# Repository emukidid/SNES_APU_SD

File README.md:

# SNES_APU_SD
Drives a SNES APU from early Super Nintendo/Super Famicom consoles with an arduino to load tracks from SD Card

Based on code written by [CaitSith2]

### Current Features
- Loads a .spc file from SD card and plays it on the SNES APU
- Loads a .spc file through the PC interface.
- 16x2 LCD for track display and menu
- Menu with file selection
- SRAM to cache tracks (CaitSith2)
- Interface APU as direct memory (CaitSith2)

### Planned Features
- RTC for nice things

### Hardware required
- Early NTSC SNES or Super Famicom with modular APU
- Arduino Mega
- APU Arduino Shield (Work In Progress)
- Love for 16-bit SNES music

[caitsith2]:  <https://www.caitsith2.com/snes/apu.htm>

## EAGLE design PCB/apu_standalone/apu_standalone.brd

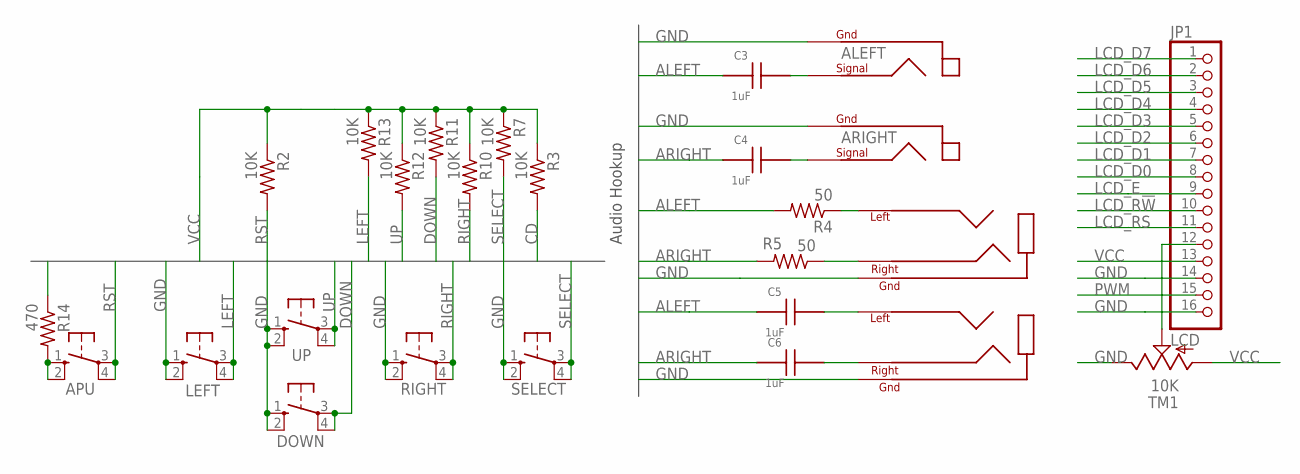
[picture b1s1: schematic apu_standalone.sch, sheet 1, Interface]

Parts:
APU: Reset; B3F-10XX
C3, C4, C5, C6: 1uF; C0805
DOWN: DOWN; B3F-10XX
JP1: LCD; 1X16
LEFT: LEFT; B3F-10XX
R2, R3, R7, R10, R11, R12, R13: 10K; R0805
R4, R5: 50; R0805
R14: 470; R0805
RIGHT: RIGHT; B3F-10XX
SELECT: SELECT; B3F-10XX
TM1: 10K; CA6H
U$2, U$3: HEADPHONE; SJ1-3533N
U$4, U$5: RCA; RCJ-01X
UP: UP; B3F-10XX

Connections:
ALEFT: C3.1, C5.1, R4.2; also elsewhere on the board
ARIGHT: C4.1, C6.1, R5.2; also elsewhere on the board
CD: R3.2; also elsewhere on the board
DOWN: DOWN.3, DOWN.4 (P1), R11.2; also elsewhere on the board
GND: DOWN.1 (S), DOWN.2 (S1), JP1.14, JP1.16, LEFT.1 (S), LEFT.2 (S1), R14.1, RIGHT.1 (S), RIGHT.2 (S1), SELECT.1 (S), SELECT.2 (S1), TM1.E, U$2.GND, U$3.GND, U$4.PGND1, U$4.PGND2, U$4.PGND3, U$5.PGND1, U$5.PGND2, U$5.PGND3, UP.1 (S), UP.2 (S1); also elsewhere on the board
LCD_D0: JP1.8; also elsewhere on the board
LCD_D1: JP1.7; also elsewhere on the board
LCD_D2: JP1.6; also elsewhere on the board
LCD_D3: JP1.5; also elsewhere on the board
LCD_D4: JP1.4; also elsewhere on the board
LCD_D5: JP1.3; also elsewhere on the board
LCD_D6: JP1.2; also elsewhere on the board
LCD_D7: JP1.1; also elsewhere on the board
LCD_E: JP1.9; also elsewhere on the board
LCD_R!W: JP1.10; also elsewhere on the board
LCD_RS: JP1.11; also elsewhere on the board
LEFT: LEFT.3, LEFT.4 (P1), R13.2; also elsewhere on the board
unnamed: C3.2, U$4.PSIG
unnamed: C4.2, U$5.PSIG
unnamed: C5.2, U$3.LEFT
unnamed: APU.1 (S), APU.2 (S1), R14.2
unnamed: C6.2, U$3.RIGHT
unnamed: R4.1, U$2.LEFT
unnamed: R5.1, U$2.RIGHT
unnamed: JP1.12, TM1.S
PWM: JP1.15; also elsewhere on the board
RIGHT: R10.2, RIGHT.3, RIGHT.4 (P1); also elsewhere on the board
RST: APU.3, APU.4 (P1), R2.2; also elsewhere on the board
SELECT: R7.2, SELECT.3, SELECT.4 (P1); also elsewhere on the board
UP: R12.2, UP.3, UP.4 (P1); also elsewhere on the board
VCC: JP1.13, R2.1, R3.1, R7.1, R10.1, R11.1, R12.1, R13.1, TM1.A; also elsewhere on the board

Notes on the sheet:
Audio Hookup

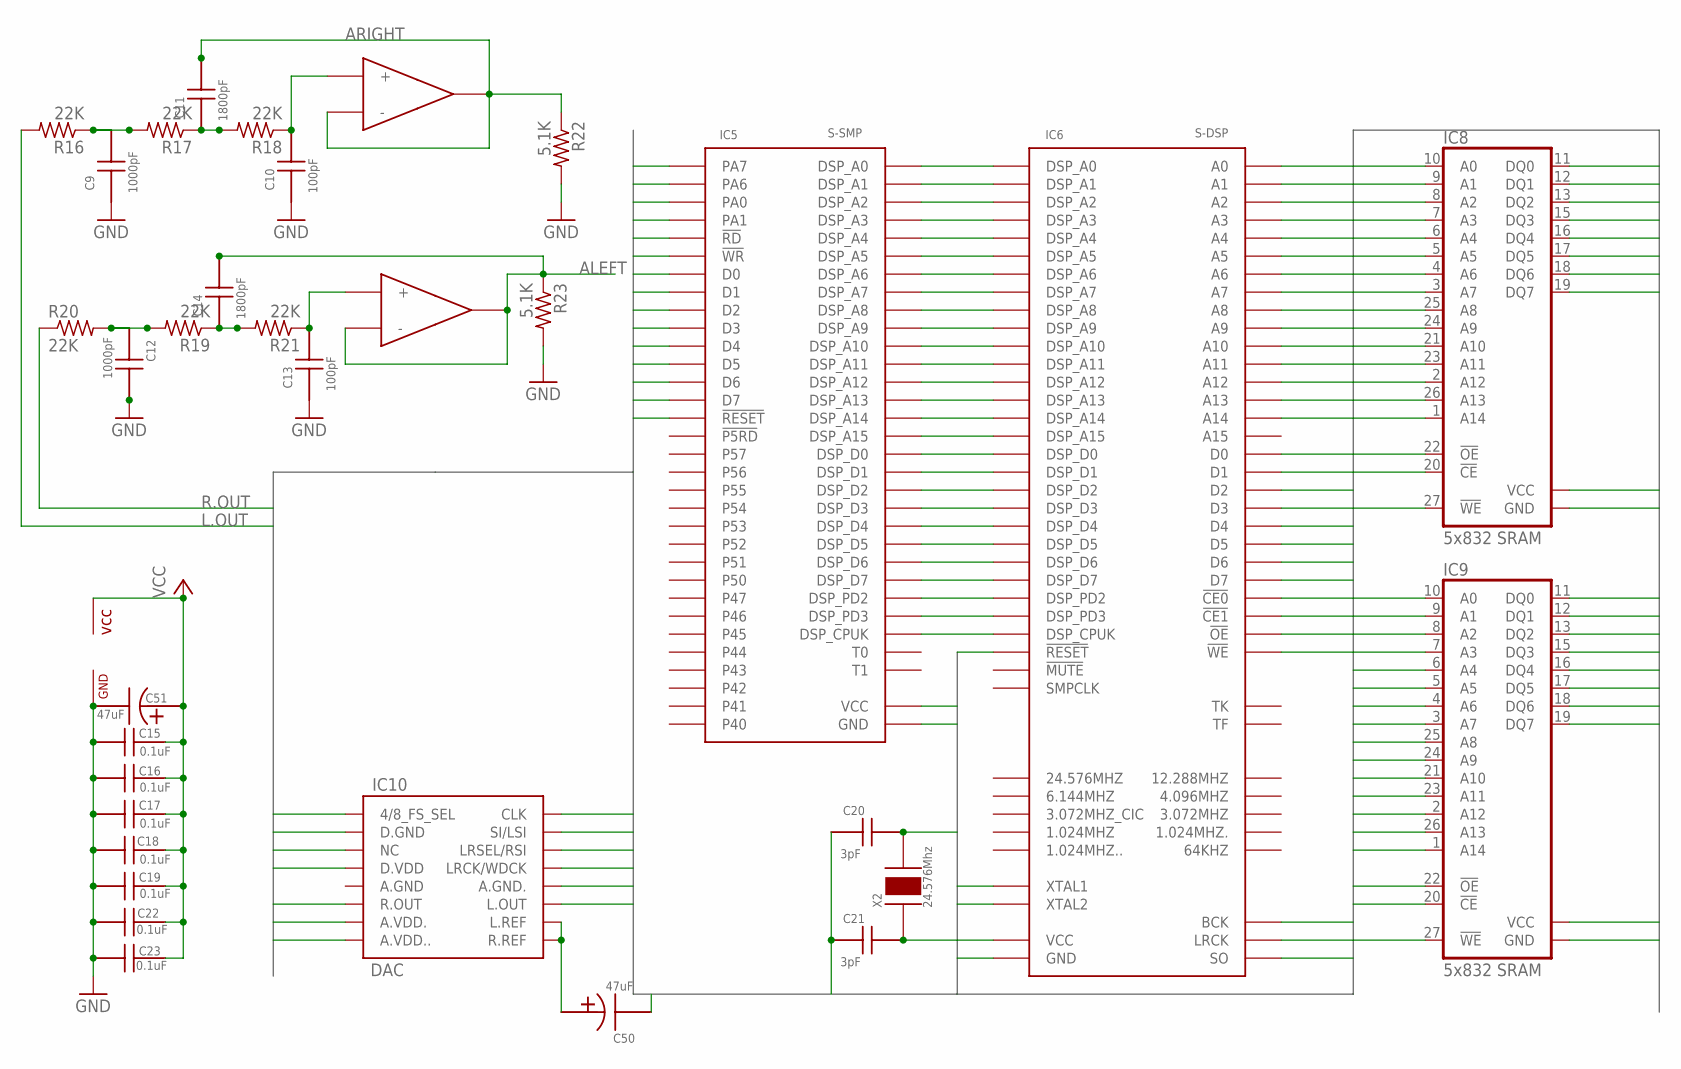
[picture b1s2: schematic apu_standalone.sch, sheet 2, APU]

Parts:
C9, C12: 1000pF; C0805
C10, C13: 100pF; C0805
C11, C14: 1800pF; C0805
C15, C16, C17, C18, C19, C22, C23: 0.1uF; C0805
C20, C21: 3pF; C0805
C50, C51: 47uF; TT5D6
IC5: S-SMP; QFP64_SOT319
IC6: S-DSP; QFP80_SOT318
IC7: LM2904; SO-08
IC8, IC9: 5x832 SRAM; SO28X
IC10: DAC; SO16W
R16, R17, R18, R19, R20, R21: 22K; R0805
R22, R23: 5.1K; R0805
X2: 24.576Mhz; QS

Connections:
!CE0: IC6.28 (!CE0), IC8.20 (!CE)
!CE1: IC6.27 (!CE1), IC9.20 (!CE)
!OE: IC6.30 (!OE), IC8.22 (!OE), IC9.22 (!OE)
!RD: IC5.46 (!RD); also elsewhere on the board
!WE: IC6.36 (!WE), IC8.27 (!WE), IC9.27 (!WE)
!WR: IC5.47 (!WR); also elsewhere on the board
A10: IC5.49 (PA0); also elsewhere on the board
A11: IC5.48 (PA1); also elsewhere on the board
A15: IC5.51 (PA7); also elsewhere on the board
A18: IC6.9 (A0), IC8.10 (A0), IC9.10 (A0)
A19: IC6.10 (A1), IC8.9 (A1), IC9.9 (A1)
A20: IC6.11 (A2), IC8.8 (A2), IC9.8 (A2)
A21: IC6.13 (A3), IC8.7 (A3), IC9.7 (A3)
A22: IC6.14 (A4), IC8.6 (A4), IC9.6 (A4)
A23: IC6.15 (A5), IC8.5 (A5), IC9.5 (A5)
A24: IC6.16 (A6), IC8.4 (A6), IC9.4 (A6)
A25: IC6.17 (A7), IC8.3 (A7), IC9.3 (A7)
A26: IC6.34 (A8), IC8.25 (A8), IC9.25 (A8)
A27: IC6.32 (A9), IC8.24 (A9), IC9.24 (A9)
A28: IC6.29 (A10), IC8.21 (A10), IC9.21 (A10)
A29: IC6.31 (A11), IC8.23 (A11), IC9.23 (A11)
A30: IC6.18 (A12), IC8.2 (A12), IC9.2 (A12)
A31: IC6.35 (A13), IC8.26 (A13), IC9.26 (A13)
A32: IC6.19 (A14), IC8.1 (A14), IC9.1 (A14)
A.REF: C50.+, IC10.9 (R.REF), IC10.10 (L.REF)
ALEFT: C14.2, IC7.6 (-), IC7.7 (OUT), R23.1; also elsewhere on the board
ARIGHT: C11.2, IC7.1 (OUT), IC7.2 (-), R22.1; also elsewhere on the board
BCK: IC6.42 (BCK), IC10.16 (CLK)
D0: IC5.45 (D0); also elsewhere on the board
D1: IC5.44 (D1); also elsewhere on the board
D2: IC5.43 (D2); also elsewhere on the board
D3: IC5.42 (D3); also elsewhere on the board
D4: IC5.41 (D4); also elsewhere on the board
D5: IC5.40 (D5); also elsewhere on the board
D6: IC5.39 (D6); also elsewhere on the board
D7: IC5.38 (D7); also elsewhere on the board
D8: IC6.8 (D0), IC8.11 (DQ0), IC9.11 (DQ0)
D9: IC6.7 (D1), IC8.12 (DQ1), IC9.12 (DQ1)
D10: IC6.6 (D2), IC8.13 (DQ2), IC9.13 (DQ2)
D11: IC6.22 (D3), IC8.15 (DQ3), IC9.15 (DQ3)
D12: IC6.23 (D4), IC8.16 (DQ4), IC9.16 (DQ4)
D13: IC6.24 (D5), IC8.17 (DQ5), IC9.17 (DQ5)
D14: IC6.25 (D6), IC8.18 (DQ6), IC9.18 (DQ6)
D15: IC6.26 (D7), IC8.19 (DQ7), IC9.19 (DQ7)
DSP_A0: IC5.5 (DSP_A0), IC6.60 (DSP_A0)
DSP_A1: IC5.4 (DSP_A1), IC6.61 (DSP_A1)
DSP_A2: IC5.3 (DSP_A2), IC6.62 (DSP_A2)
DSP_A3: IC5.2 (DSP_A3), IC6.63 (DSP_A3)
DSP_A4: IC5.1 (DSP_A4), IC6.64 (DSP_A4)
DSP_A5: IC5.64 (DSP_A5), IC6.65 (DSP_A5)
DSP_A6: IC5.63 (DSP_A6), IC6.66 (DSP_A6)
DSP_A7: IC5.62 (DSP_A7), IC6.67 (DSP_A7)
DSP_A8: IC5.61 (DSP_A8), IC6.68 (DSP_A8)
DSP_A9: IC5.60 (DSP_A9), IC6.69 (DSP_A9)
DSP_A10: IC5.59 (DSP_A10), IC6.70 (DSP_A10)
DSP_A11: IC5.56 (DSP_A11), IC6.71 (DSP_A11)
DSP_A12: IC5.55 (DSP_A12), IC6.72 (DSP_A12)
DSP_A13: IC5.54 (DSP_A13), IC6.74 (DSP_A13)
DSP_A14: IC5.53 (DSP_A14), IC6.75 (DSP_A14)
DSP_A15: IC5.52 (DSP_A15), IC6.76 (DSP_A15)
DSP_CPUK: IC5.16 (DSP_CPUK), IC6.48 (DSP_CPUK)
DSP_D0: IC5.13 (DSP_D0), IC6.51 (DSP_D0)
DSP_D1: IC5.12 (DSP_D1), IC6.53 (DSP_D1)
DSP_D2: IC5.11 (DSP_D2), IC6.54 (DSP_D2)
DSP_D3: IC5.10 (DSP_D3), IC6.55 (DSP_D3)
DSP_D4: IC5.9 (DSP_D4), IC6.56 (DSP_D4)
DSP_D5: IC5.8 (DSP_D5), IC6.57 (DSP_D5)
DSP_D6: IC5.7 (DSP_D6), IC6.58 (DSP_D6)
DSP_D7: IC5.6 (DSP_D7), IC6.59 (DSP_D7)
DSP_PD2: IC5.15 (DSP_PD2), IC6.49 (DSP_PD2)
DSP_PD3: IC5.14 (DSP_PD3), IC6.50 (DSP_PD3)
GND: C9.1, C10.1, C12.2, C13.1, C15.2, C16.2, C17.2, C18.2, C19.2, C20.1, C21.1, C22.1, C23.2, C50.-, C51.-, IC5.26 (GND), IC5.58 (GND), IC6.12 (GND), IC6.52 (GND), IC7.4 (GND), IC8.14 (GND), IC9.14 (GND), IC10.1 (4/8_FS_SEL), IC10.2 (D.GND), IC10.12 (A.GND.), IC10.14 (LRSEL/RSI), R22.2, R23.2; also elsewhere on the board
L1: C12.1, R19.2, R20.2
L2: C14.1, R19.1, R21.2
L3: C13.2, IC7.5 (+), R21.1
L.OUT: IC10.11 (L.OUT), R16.2
LRCK: IC6.43 (LRCK), IC10.13 (LRCK/WDCK)
R1: C9.2, R16.1, R17.2
R2: C11.1, R17.1, R18.2
R3: C10.2, IC7.3 (+), R18.1
R.OUT: IC10.6 (R.OUT), R20.1
RST: IC5.37 (!RESET), IC6.47 (!RESET); also elsewhere on the board
SO: IC6.44 (SO), IC10.15 (SI/LSI)
VCC: C15.1, C16.1, C17.1, C18.1, C19.1, C22.2, C23.1, C51.+, IC5.50 (PA6), IC5.57 (VCC), IC6.33 (VCC), IC6.73 (VCC), IC7.8 (VCC), IC8.28 (VCC), IC9.28 (VCC), IC10.3 (NC), IC10.4 (D.VDD), IC10.7 (A.VDD.), IC10.8 (A.VDD..); also elsewhere on the board
XTAL1: C21.2, IC6.45 (XTAL1), X2.1
XTAL2: C20.2, IC6.46 (XTAL2), X2.2

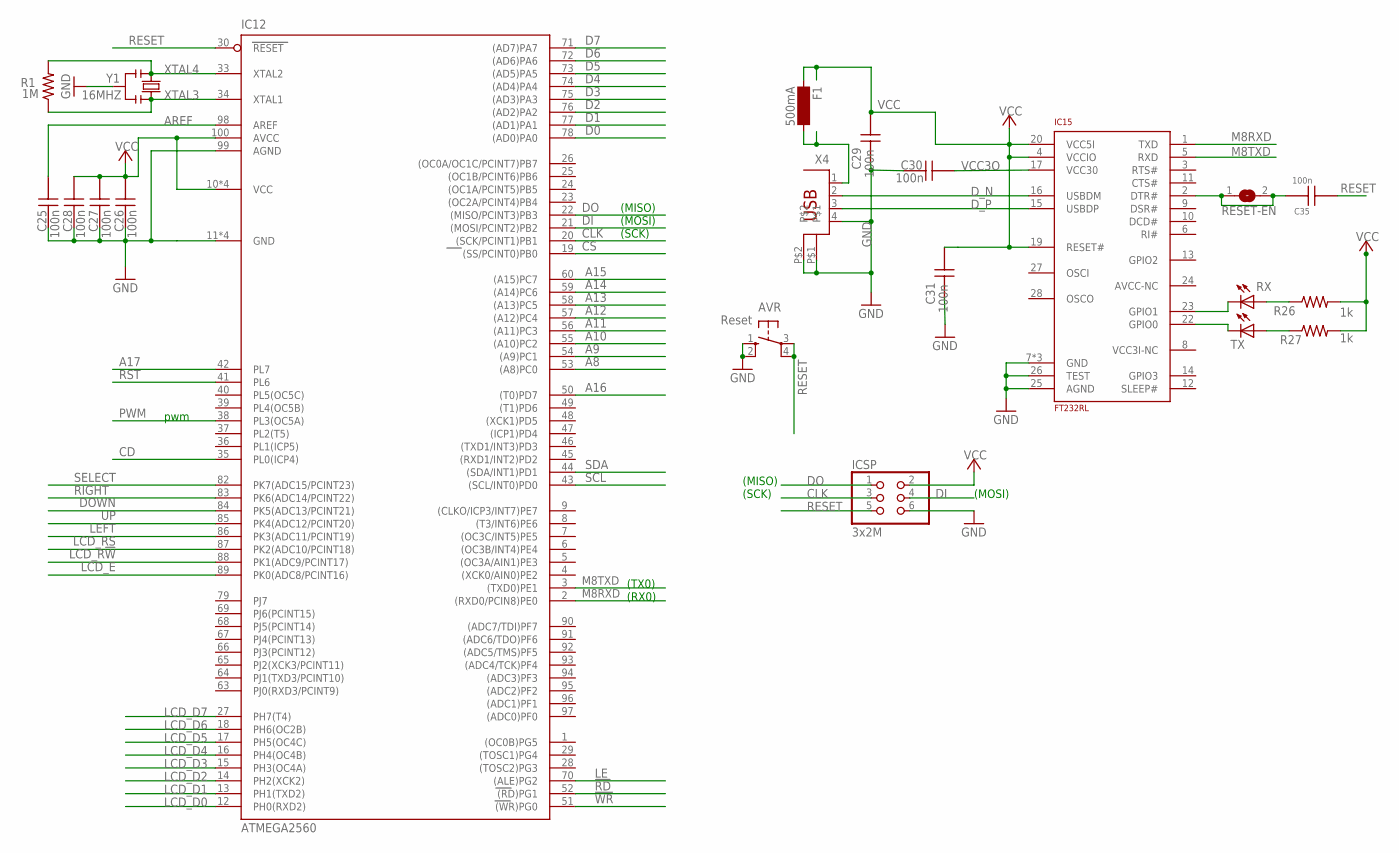
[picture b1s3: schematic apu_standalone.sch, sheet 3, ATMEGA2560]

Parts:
AVR: Reset; B3F-10XX
C25, C26, C27, C28, C29, C30, C31, C35: 100n; C0805
F1: 500mA; SM-1206
IC12: ATMEGA2560; TQFP100
IC15: FT232RL; SSOP28
ICSP: 3x2M; 2X03
R1: 1M; R0805
R26, R27: 1k; R0805
RESET-EN: SJ
RX: LEDCHIP-LED0805; CHIP-LED0805
TX: LEDCHIP-LED0805; CHIP-LED0805
X4: PN61729
Y1: 16MHZ; RESONATOR

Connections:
!RD: IC12.52 ((RD)PG1); also elsewhere on the board
!WR: IC12.51 ((WR)PG0); also elsewhere on the board
A8: IC12.53 ((A8)PC0); also elsewhere on the board
A9: IC12.54 ((A9)PC1); also elsewhere on the board
A10: IC12.55 ((A10)PC2); also elsewhere on the board
A11: IC12.56 ((A11)PC3); also elsewhere on the board
A12: IC12.57 ((A12)PC4); also elsewhere on the board
A13: IC12.58 ((A13)PC5); also elsewhere on the board
A14: IC12.59 ((A14)PC6); also elsewhere on the board
A15: IC12.60 ((A15)PC7); also elsewhere on the board
A16: IC12.50 ((T0)PD7); also elsewhere on the board
A17: IC12.42 (PL7); also elsewhere on the board
AREF: C25.1, IC12.98 (AREF)
CD: IC12.35 (PL0(ICP4)); also elsewhere on the board
CLK: IC12.20 ((SCK/PCINT1)PB1), ICSP.3; also elsewhere on the board
CS: IC12.19 ((SS/PCINT0)PB0); also elsewhere on the board
D0: IC12.78 ((AD0)PA0); also elsewhere on the board
D1: IC12.77 ((AD1)PA1); also elsewhere on the board
D2: IC12.76 ((AD2)PA2); also elsewhere on the board
D3: IC12.75 ((AD3)PA3); also elsewhere on the board
D4: IC12.74 ((AD4)PA4); also elsewhere on the board
D5: IC12.73 ((AD5)PA5); also elsewhere on the board
D6: IC12.72 ((AD6)PA6); also elsewhere on the board
D7: IC12.71 ((AD7)PA7); also elsewhere on the board
DI: IC12.21 ((MOSI/PCINT2)PB2), ICSP.4; also elsewhere on the board
DO: IC12.22 ((MISO/PCINT3)PB3), ICSP.1; also elsewhere on the board
DOWN: IC12.84 (PK5(ADC13/PCINT21)); also elsewhere on the board
DTR: C35.1, IC15.2 (DTR#), RESET-EN.1, RESET-EN.2
D_N: IC15.16 (USBDM), X4.2
D_P: IC15.15 (USBDP), X4.3
GND: AVR.1 (S), AVR.2 (S1), C25.2, C26.2, C27.2, C28.2, C29.2, C30.1, C31.2, IC12.11 (GND), IC12.32 (GND), IC12.62 (GND), IC12.81 (GND), IC12.99 (AGND), IC15.7 (GND), IC15.18 (GND), IC15.21 (GND), IC15.25 (AGND), IC15.26 (TEST), ICSP.6, X4.4, X4.P$1, X4.P$2, Y1.2; also elsewhere on the board
LCD_D0: IC12.12 (PH0(RXD2)); also elsewhere on the board
LCD_D1: IC12.13 (PH1(TXD2)); also elsewhere on the board
LCD_D2: IC12.14 (PH2(XCK2)); also elsewhere on the board
LCD_D3: IC12.15 (PH3(OC4A)); also elsewhere on the board
LCD_D4: IC12.16 (PH4(OC4B)); also elsewhere on the board
LCD_D5: IC12.17 (PH5(OC4C)); also elsewhere on the board
LCD_D6: IC12.18 (PH6(OC2B)); also elsewhere on the board
LCD_D7: IC12.27 (PH7(T4)); also elsewhere on the board
LCD_E: IC12.89 (PK0(ADC8/PCINT16)); also elsewhere on the board
LCD_R!W: IC12.88 (PK1(ADC9/PCINT17)); also elsewhere on the board
LCD_RS: IC12.87 (PK2(ADC10/PCINT18)); also elsewhere on the board
LE: IC12.70 ((ALE)PG2); also elsewhere on the board
LEFT: IC12.86 (PK3(ADC11/PCINT19)); also elsewhere on the board
M8RXD: IC12.2 ((RXD0/PCIN8)PE0), IC15.1 (TXD)
M8TXD: IC12.3 ((TXD0)PE1), IC15.5 (RXD)
unnamed: IC15.23 (GPIO1), RX.C
unnamed: IC15.22 (GPIO0), TX.C
unnamed: R26.1, RX.A
unnamed: R27.1, TX.A
unnamed: F1.2, X4.1
PWM: IC12.38 (PL3(OC5A)); also elsewhere on the board
RESET: AVR.3, AVR.4 (P1), C35.2, IC12.30 (RESET), ICSP.5
RIGHT: IC12.83 (PK6(ADC14/PCINT22)); also elsewhere on the board
RST: IC12.41 (PL6); also elsewhere on the board
SCL: IC12.43 ((SCL/INT0)PD0); also elsewhere on the board
SDA: IC12.44 ((SDA/INT1)PD1); also elsewhere on the board
SELECT: IC12.82 (PK7(ADC15/PCINT23)); also elsewhere on the board
UP: IC12.85 (PK4(ADC12/PCINT20)); also elsewhere on the board
VCC: C26.1, C27.1, C28.1, C29.1, C31.1, F1.1, IC12.10 (VCC), IC12.31 (VCC), IC12.61 (VCC), IC12.80 (VCC), IC12.100 (AVCC), IC15.4 (VCCIO), IC15.19 (RESET#), IC15.20 (VCC5I), ICSP.2, R26.2, R27.2; also elsewhere on the board
VCC3O: C30.2, IC15.17 (VCC30)
XTAL3: IC12.34 (XTAL1), R1.1, Y1.3
XTAL4: IC12.33 (XTAL2), R1.2, Y1.1

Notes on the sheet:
pwm
(TX0)
(RX0)
(MISO)
(SCK)
(MOSI)

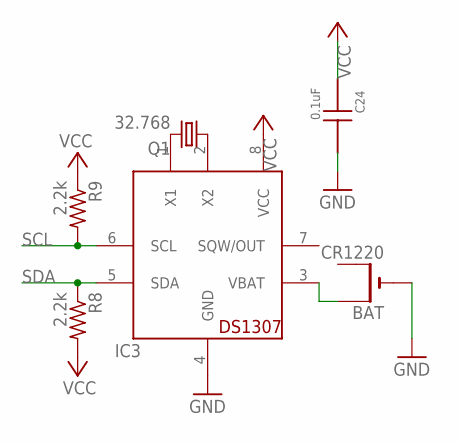
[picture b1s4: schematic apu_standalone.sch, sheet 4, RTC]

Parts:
BAT: CR1220; CR1220-SMD
C24: 0.1uF; C0805
IC3: DS1307; SO-08
Q1: 32.768; SMD
R8, R9: 2.2k; R0805

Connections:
GND: BAT.-, C24.2, IC3.4 (GND); also elsewhere on the board
unnamed: BAT.+$1 (+), IC3.3 (VBAT)
unnamed: IC3.1 (X1), Q1.2
unnamed: IC3.2 (X2), Q1.1
SCL: IC3.6 (SCL), R9.2; also elsewhere on the board
SDA: IC3.5 (SDA), R8.1; also elsewhere on the board
VCC: C24.1, IC3.8 (VCC), R8.2, R9.1; also elsewhere on the board

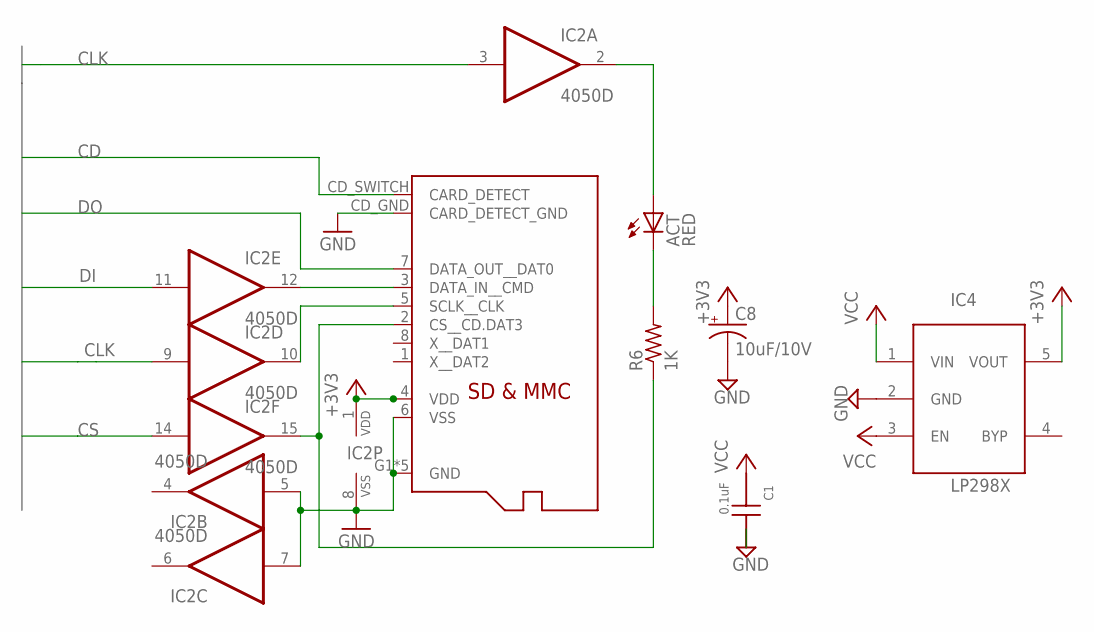
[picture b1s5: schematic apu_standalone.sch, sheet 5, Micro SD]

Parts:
ACT: RED; CHIP-LED0805
C1: 0.1uF; C0805
C8: 10uF/10V; A/3216-18R
IC2: 4050D; SO16
IC4: LP298XS; SOT23-5L
R6: 1K; R0805
U$1: MICROSD-2; MICROSD-3

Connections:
+3V3: C8.+, IC2.1 (VDD), IC4.5 (VOUT), U$1.4 (VDD)
BUF_CLK: IC2.10 (O), U$1.5 (SCLK__CLK)
BUF_CS: IC2.15 (O), R6.1, U$1.2 (CS__CD.DAT3)
BUF_DI: IC2.12 (O), U$1.3 (DATA_IN__CMD)
BUF_LED: ACT.A, IC2.2 (O)
CD: U$1.CD_SWITCH (CARD_DETECT); also elsewhere on the board
CLK: IC2.3 (I), IC2.9 (I); also elsewhere on the board
CS: IC2.14 (I); also elsewhere on the board
DI: IC2.11 (I); also elsewhere on the board
DO: U$1.7 (DATA_OUT__DAT0); also elsewhere on the board
GND: C1.2, C8.-, IC2.5 (I), IC2.7 (I), IC2.8 (VSS), IC4.2 (GND), U$1.6 (VSS), U$1.CD_GND (CARD_DETECT_GND), U$1.G1 (GND), U$1.G2 (GND), U$1.G3 (GND), U$1.G4 (GND), U$1.G5 (GND); also elsewhere on the board
unnamed: ACT.C, R6.2
VCC: C1.1, IC4.1 (VIN), IC4.3 (EN); also elsewhere on the board

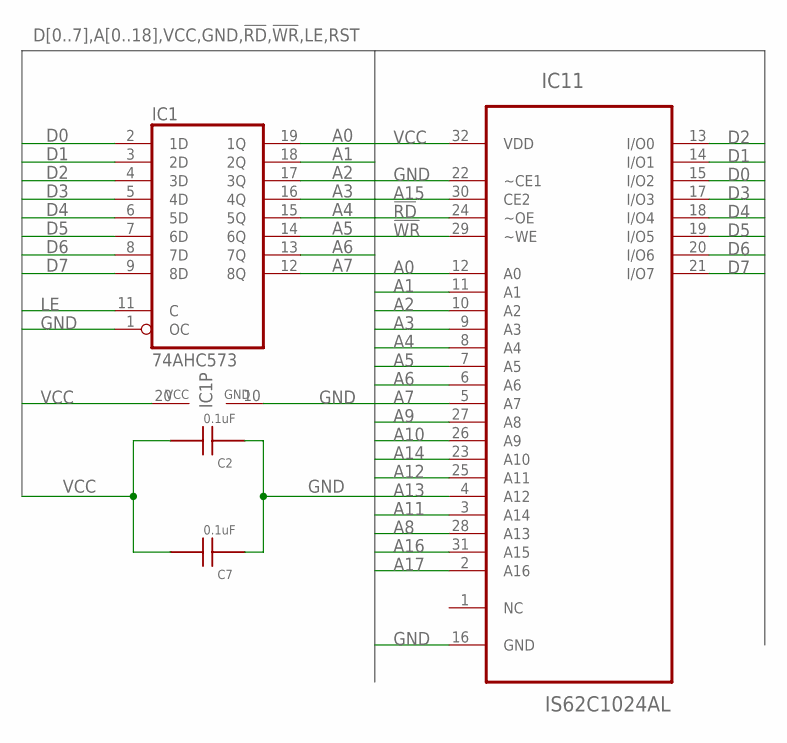
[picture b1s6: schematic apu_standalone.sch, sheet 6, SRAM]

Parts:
C2, C7: 0.1uF; C0805
IC1: 74AHC573; SO20W
IC11: IS62C1024AL; SOIC127P1412X305-32N

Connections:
!RD: IC11.24 (~OE); also elsewhere on the board
!WR: IC11.29 (~WE); also elsewhere on the board
A0: IC1.19 (1Q), IC11.12 (A0)
A1: IC1.18 (2Q), IC11.11 (A1)
A2: IC1.17 (3Q), IC11.10 (A2)
A3: IC1.16 (4Q), IC11.9 (A3)
A4: IC1.15 (5Q), IC11.8 (A4)
A5: IC1.14 (6Q), IC11.7 (A5)
A6: IC1.13 (7Q), IC11.6 (A6)
A7: IC1.12 (8Q), IC11.5 (A7)
A8: IC11.28 (A13); also elsewhere on the board
A9: IC11.27 (A8); also elsewhere on the board
A10: IC11.26 (A9); also elsewhere on the board
A11: IC11.3 (A14); also elsewhere on the board
A12: IC11.25 (A11); also elsewhere on the board
A13: IC11.4 (A12); also elsewhere on the board
A14: IC11.23 (A10); also elsewhere on the board
A15: IC11.30 (CE2); also elsewhere on the board
A16: IC11.31 (A15); also elsewhere on the board
A17: IC11.2 (A16); also elsewhere on the board
D0: IC1.2 (1D), IC11.15 (I/O2); also elsewhere on the board
D1: IC1.3 (2D), IC11.14 (I/O1); also elsewhere on the board
D2: IC1.4 (3D), IC11.13 (I/O0); also elsewhere on the board
D3: IC1.5 (4D), IC11.17 (I/O3); also elsewhere on the board
D4: IC1.6 (5D), IC11.18 (I/O4); also elsewhere on the board
D5: IC1.7 (6D), IC11.19 (I/O5); also elsewhere on the board
D6: IC1.8 (7D), IC11.20 (I/O6); also elsewhere on the board
D7: IC1.9 (8D), IC11.21 (I/O7); also elsewhere on the board
GND: C2.1, C7.1, IC1.1 (OC), IC1.10 (GND), IC11.16 (GND), IC11.22 (~CE1); also elsewhere on the board
LE: IC1.11 (C); also elsewhere on the board
VCC: C2.2, C7.2, IC1.20 (VCC), IC11.32 (VDD); also elsewhere on the board

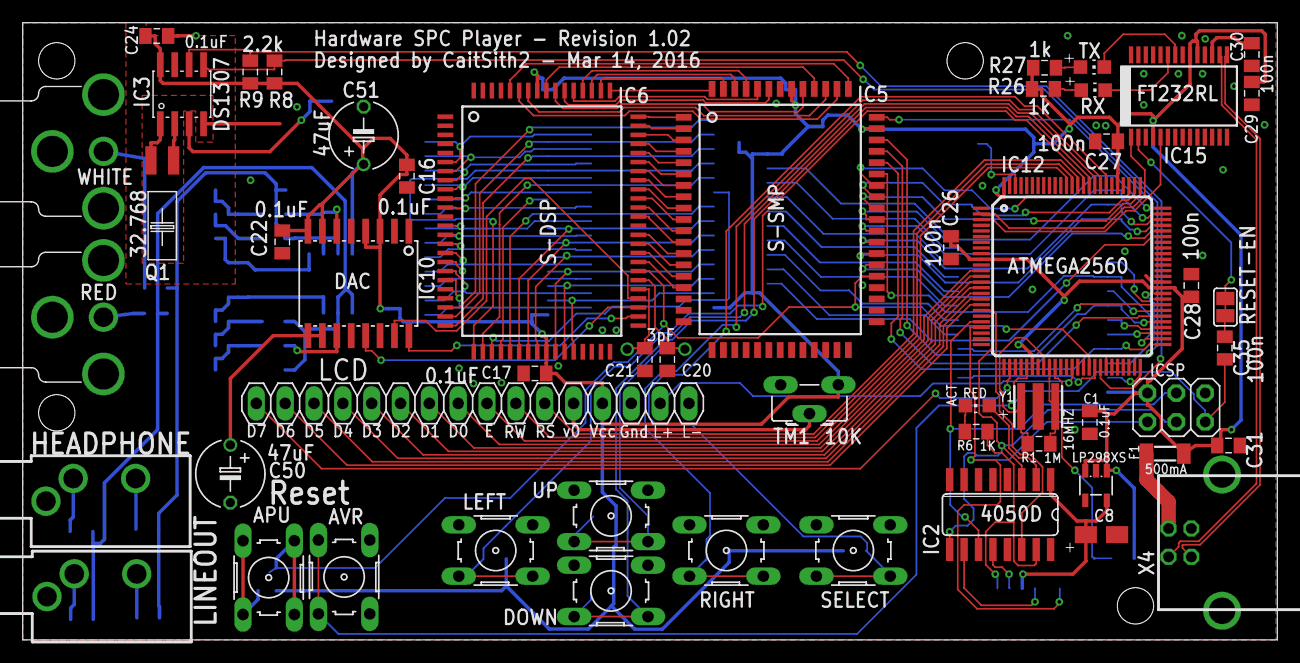
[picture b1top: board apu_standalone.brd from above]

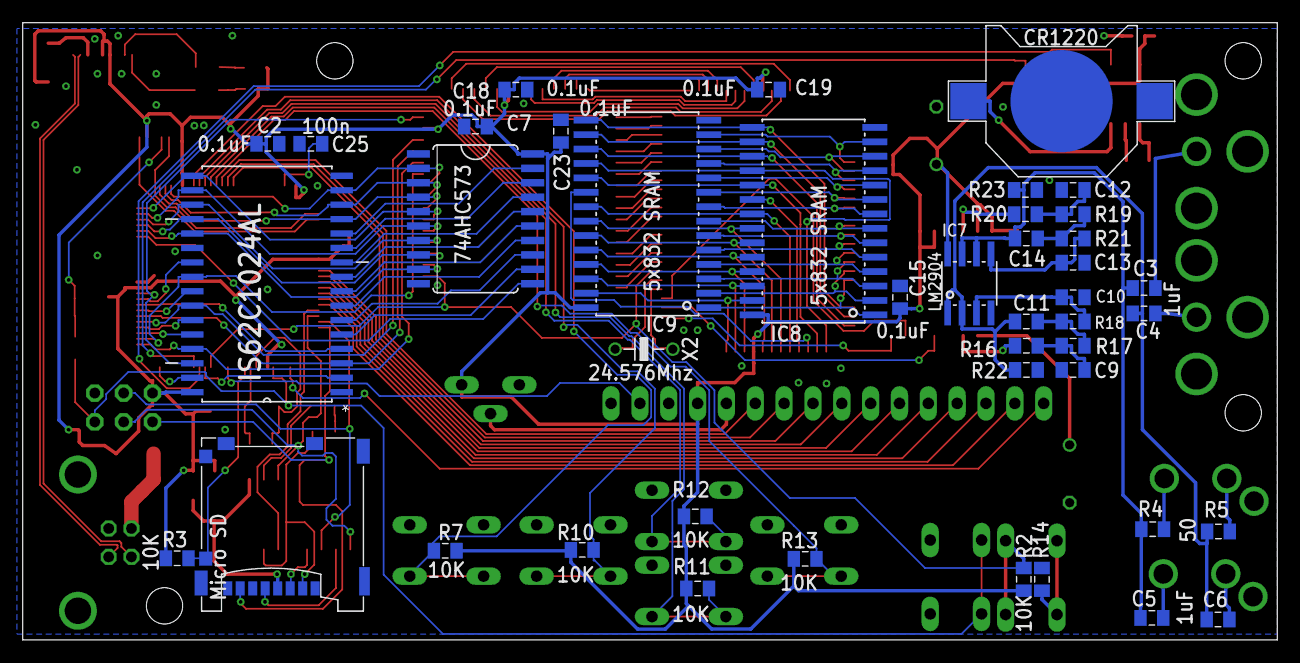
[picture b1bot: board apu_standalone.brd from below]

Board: 2 copper layers, 110.5 x 54.4 mm, 96 parts (43 on the bottom side), 158 nets.

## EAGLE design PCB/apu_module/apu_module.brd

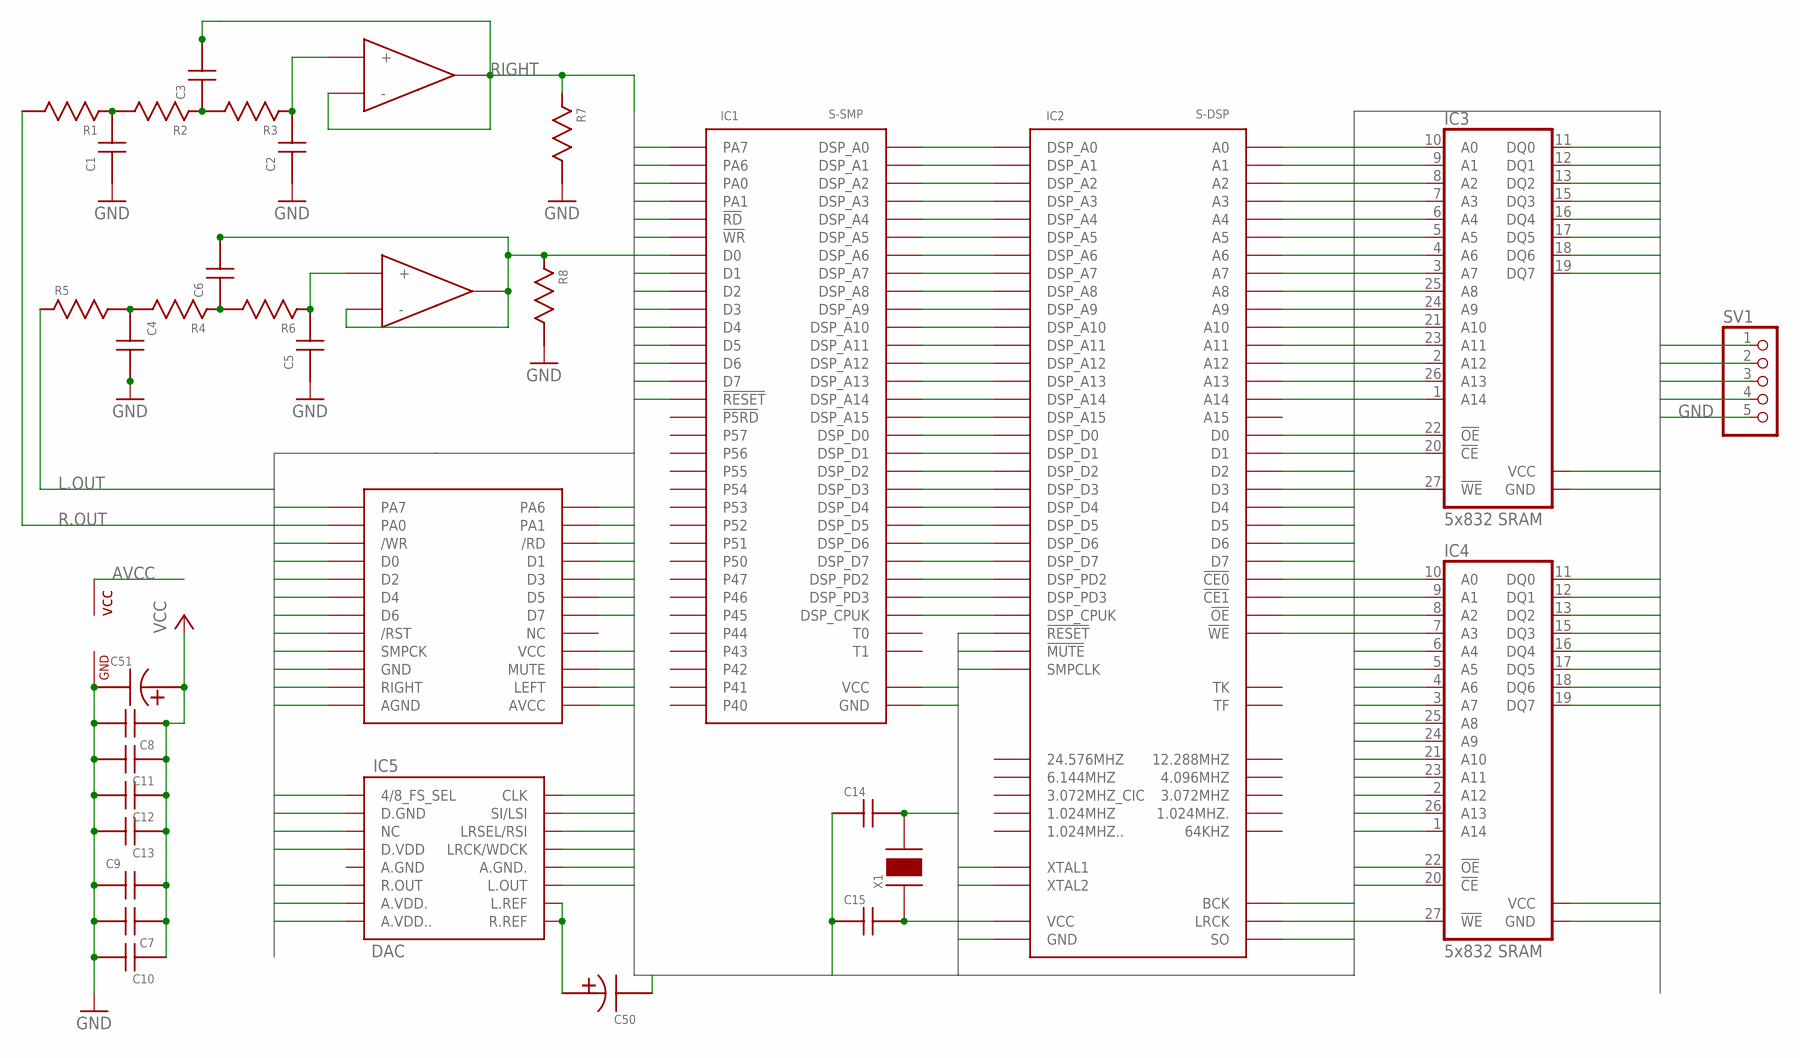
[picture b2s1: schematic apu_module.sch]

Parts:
C1, C2, C3, C4, C5, C6, C7, C8, C9, C10, C11, C12, C13, C14, C15: C0805
C50, C51: CAPACITOR; TT5D6
E$3: APU
IC1: S-SMP; QFP64_SOT319
IC2: S-DSP; QFP80_SOT318
IC3, IC4: 5x832 SRAM; SO28X
IC5: DAC; SO16W
IC6: LM2904; SO-08
R1, R2, R3, R4, R5, R6, R7, R8: R0805
SV1: PINHD-1X5; 1X05
X1: CRYSTAL; QS

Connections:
!CE0: IC2.28 (!CE0), IC3.20 (!CE)
!CE1: IC2.27 (!CE1), IC4.20 (!CE)
!MUTE: E$3.P$20 (MUTE), IC2.39 (!MUTE)
!OE: IC2.30 (!OE), IC3.22 (!OE), IC4.22 (!OE)
!P_RD: E$3.P$6 (/RD), IC1.46 (!RD)
!P_WR: E$3.P$5 (/WR), IC1.47 (!WR)
!RESET: E$3.P$15 (/RST), IC1.37 (!RESET), IC2.47 (!RESET)
!WE: IC2.36 (!WE), IC3.27 (!WE), IC4.27 (!WE)
A0: IC2.9 (A0), IC3.10 (A0), IC4.10 (A0)
A1: IC2.10 (A1), IC3.9 (A1), IC4.9 (A1)
A2: IC2.11 (A2), IC3.8 (A2), IC4.8 (A2)
A3: IC2.13 (A3), IC3.7 (A3), IC4.7 (A3)
A4: IC2.14 (A4), IC3.6 (A4), IC4.6 (A4)
A5: IC2.15 (A5), IC3.5 (A5), IC4.5 (A5)
A6: IC2.16 (A6), IC3.4 (A6), IC4.4 (A6)
A7: IC2.17 (A7), IC3.3 (A7), IC4.3 (A7)
A8: IC2.34 (A8), IC3.25 (A8), IC4.25 (A8)
A9: IC2.32 (A9), IC3.24 (A9), IC4.24 (A9)
A10: IC2.29 (A10), IC3.21 (A10), IC4.21 (A10)
A11: IC2.31 (A11), IC3.23 (A11), IC4.23 (A11)
A12: IC2.18 (A12), IC3.2 (A12), IC4.2 (A12)
A13: IC2.35 (A13), IC3.26 (A13), IC4.26 (A13)
A14: IC2.19 (A14), IC3.1 (A14), IC4.1 (A14)
A.REF: C50.+, IC5.9 (R.REF), IC5.10 (L.REF)
AVCC: E$3.P$24 (AVCC), IC6.8 (VCC)
BCK: IC2.42 (BCK), IC5.16 (CLK), SV1.4
D0: IC2.8 (D0), IC3.11 (DQ0), IC4.11 (DQ0)
D1: IC2.7 (D1), IC3.12 (DQ1), IC4.12 (DQ1)
D2: IC2.6 (D2), IC3.13 (DQ2), IC4.13 (DQ2)
D3: IC2.22 (D3), IC3.15 (DQ3), IC4.15 (DQ3)
D4: IC2.23 (D4), IC3.16 (DQ4), IC4.16 (DQ4)
D5: IC2.24 (D5), IC3.17 (DQ5), IC4.17 (DQ5)
D6: IC2.25 (D6), IC3.18 (DQ6), IC4.18 (DQ6)
D7: IC2.26 (D7), IC3.19 (DQ7), IC4.19 (DQ7)
DSP_A0: IC1.5 (DSP_A0), IC2.60 (DSP_A0)
DSP_A1: IC1.4 (DSP_A1), IC2.61 (DSP_A1)
DSP_A2: IC1.3 (DSP_A2), IC2.62 (DSP_A2)
DSP_A3: IC1.2 (DSP_A3), IC2.63 (DSP_A3)
DSP_A4: IC1.1 (DSP_A4), IC2.64 (DSP_A4)
DSP_A5: IC1.64 (DSP_A5), IC2.65 (DSP_A5)
DSP_A6: IC1.63 (DSP_A6), IC2.66 (DSP_A6)
DSP_A7: IC1.62 (DSP_A7), IC2.67 (DSP_A7)
DSP_A8: IC1.61 (DSP_A8), IC2.68 (DSP_A8)
DSP_A9: IC1.60 (DSP_A9), IC2.69 (DSP_A9)
DSP_A10: IC1.59 (DSP_A10), IC2.70 (DSP_A10)
DSP_A11: IC1.56 (DSP_A11), IC2.71 (DSP_A11)
DSP_A12: IC1.55 (DSP_A12), IC2.72 (DSP_A12)
DSP_A13: IC1.54 (DSP_A13), IC2.74 (DSP_A13)
DSP_A14: IC1.53 (DSP_A14), IC2.75 (DSP_A14)
DSP_A15: IC1.52 (DSP_A15), IC2.76 (DSP_A15)
DSP_CPUK: IC1.16 (DSP_CPUK), IC2.48 (DSP_CPUK)
DSP_D0: IC1.13 (DSP_D0), IC2.51 (DSP_D0)
DSP_D1: IC1.12 (DSP_D1), IC2.53 (DSP_D1)
DSP_D2: IC1.11 (DSP_D2), IC2.54 (DSP_D2)
DSP_D3: IC1.10 (DSP_D3), IC2.55 (DSP_D3)
DSP_D4: IC1.9 (DSP_D4), IC2.56 (DSP_D4)
DSP_D5: IC1.8 (DSP_D5), IC2.57 (DSP_D5)
DSP_D6: IC1.7 (DSP_D6), IC2.58 (DSP_D6)
DSP_D7: IC1.6 (DSP_D7), IC2.59 (DSP_D7)
DSP_PD2: IC1.15 (DSP_PD2), IC2.49 (DSP_PD2)
DSP_PD3: IC1.14 (DSP_PD3), IC2.50 (DSP_PD3)
GND: C1.1, C2.1, C4.2, C5.1, C7.2, C8.2, C9.1, C10.2, C11.2, C12.2, C13.2, C14.1, C15.1, C50.-, C51.-, E$3.P$19 (GND), E$3.P$23 (AGND), IC1.26 (GND), IC1.58 (GND), IC2.12 (GND), IC2.52 (GND), IC3.14 (GND), IC4.14 (GND), IC5.1 (4/8_FS_SEL), IC5.2 (D.GND), IC5.12 (A.GND.), IC5.14 (LRSEL/RSI), IC6.4 (GND), R7.2, R8.2, SV1.5
L1: C4.1, R4.2, R5.2
L2: C6.1, R4.1, R6.2
L3: C5.2, IC6.5 (+), R6.1
L.OUT: IC5.11 (L.OUT), R5.1
LEFT: C6.2, E$3.P$21 (LEFT), IC6.6 (-), IC6.7 (OUT), R8.1
LRCK: IC2.43 (LRCK), IC5.13 (LRCK/WDCK), SV1.3
PA0: E$3.P$3 (PA0), IC1.49 (PA0)
PA1: E$3.P$4 (PA1), IC1.48 (PA1)
PA6: E$3.P$2 (PA6), IC1.50 (PA6)
PA7: E$3.P$1 (PA7), IC1.51 (PA7)
PD0: E$3.P$7 (D0), IC1.45 (D0)
PD1: E$3.P$8 (D1), IC1.44 (D1)
PD2: E$3.P$9 (D2), IC1.43 (D2)
PD3: E$3.P$10 (D3), IC1.42 (D3)
PD4: E$3.P$11 (D4), IC1.41 (D4)
PD5: E$3.P$12 (D5), IC1.40 (D5)
PD6: E$3.P$13 (D6), IC1.39 (D6)
PD7: E$3.P$14 (D7), IC1.38 (D7)
R1: C1.2, R1.1, R2.2
R2: C3.1, R2.1, R3.2
R3: C2.2, IC6.3 (+), R3.1
R.OUT: IC5.6 (R.OUT), R1.2
RIGHT: C3.2, E$3.P$22 (RIGHT), IC6.1 (OUT), IC6.2 (-), R7.1
SMPCLK: E$3.P$17 (SMPCK), IC2.78 (SMPCLK)
SO: IC2.44 (SO), IC5.15 (SI/LSI), SV1.2
VCC: C7.1, C8.1, C9.2, C10.1, C11.1, C12.1, C13.1, C51.+, E$3.P$18 (VCC), IC1.57 (VCC), IC2.33 (VCC), IC2.73 (VCC), IC3.28 (VCC), IC4.28 (VCC), IC5.3 (NC), IC5.4 (D.VDD), IC5.7 (A.VDD.), IC5.8 (A.VDD..), SV1.1
XTAL1: C15.2, IC2.45 (XTAL1), X1.1
XTAL2: C14.2, IC2.46 (XTAL2), X1.2

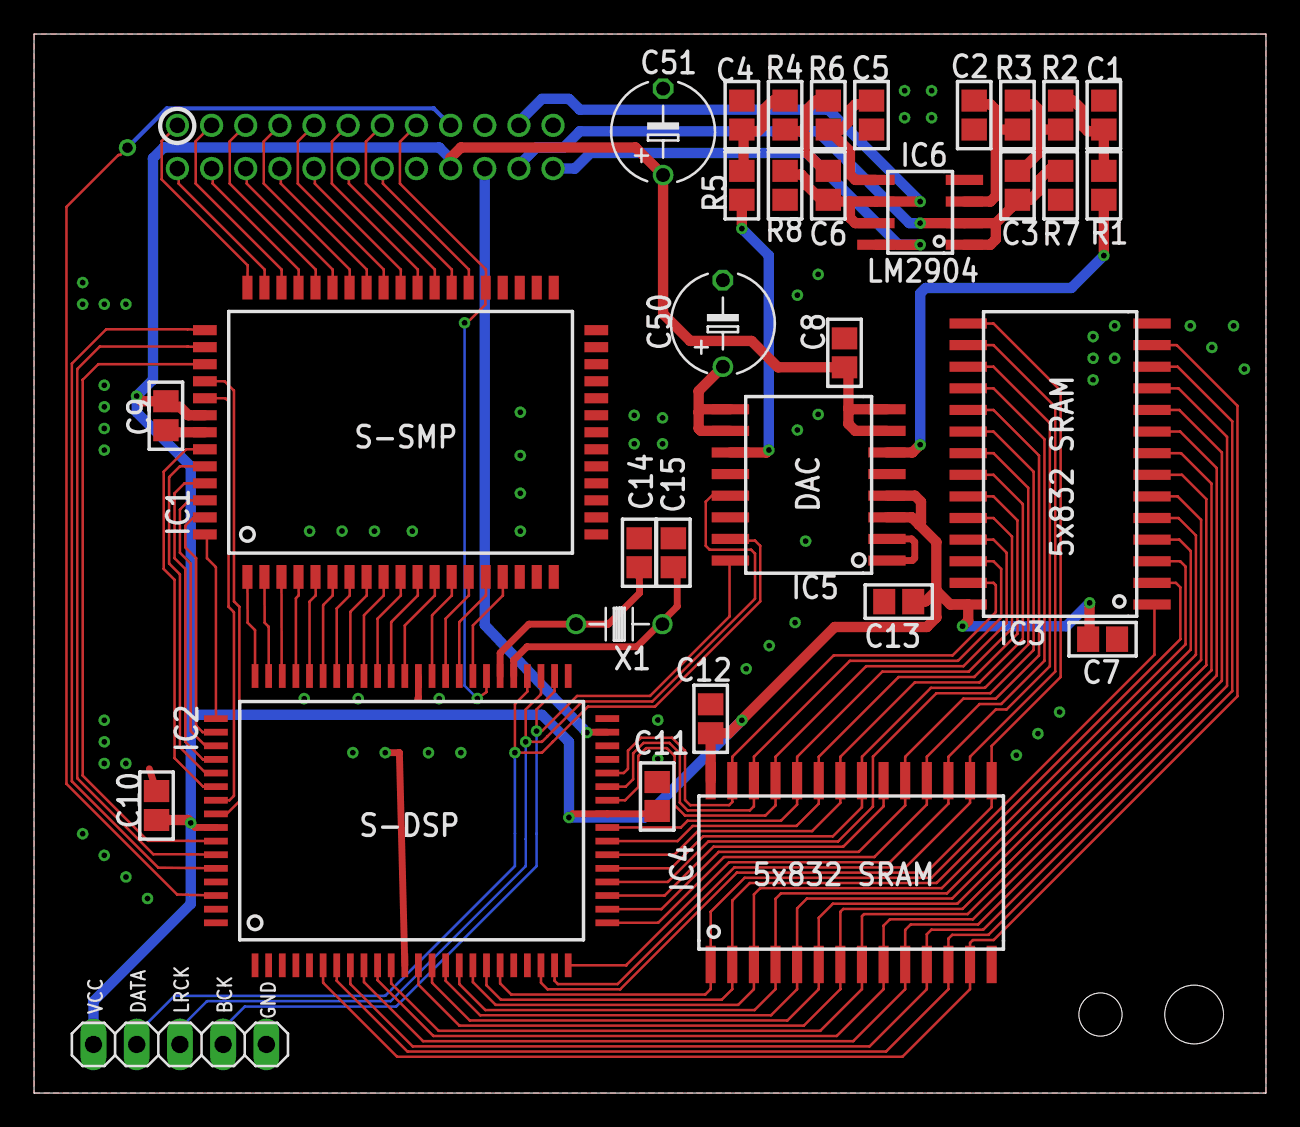
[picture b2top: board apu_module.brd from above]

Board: 2 copper layers, 72.4 x 62.2 mm, 34 parts (1 on the bottom side), 90 nets.
